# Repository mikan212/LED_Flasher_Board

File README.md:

# LED_Flasher_Board

入力電圧3V
Q1とQ2は裏返してハンダ付けでしてください
| 番号 | 部品 | URL |
|---|---|---|
|R1-R4|390Ω|https://akizukidenshi.com/catalog/g/g125391/|
|R5,R6|10kΩ|https://akizukidenshi.com/catalog/g/g116103/|
|LED|OSW4XME1C1E-100|https://akizukidenshi.com/catalog/g/g106853/|
|C1,C2|100uF|https://akizukidenshi.com/catalog/g/g117877/|
|Q1,Q2|2SD2012|https://akizukidenshi.com/catalog/g/g102510/|
|コネクタ|XH2Pin|https://akizukidenshi.com/catalog/g/g112247/|

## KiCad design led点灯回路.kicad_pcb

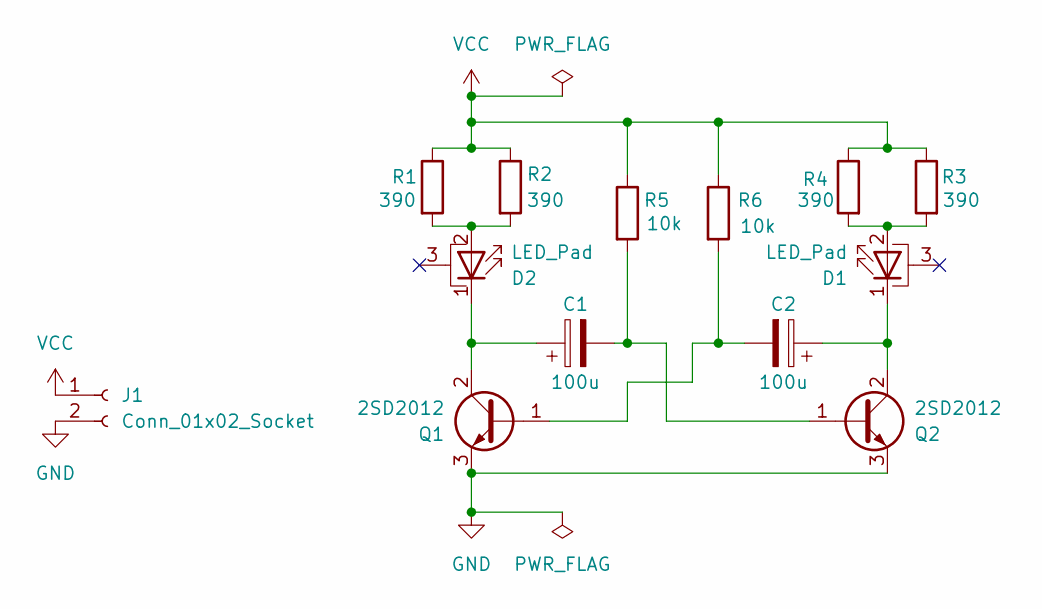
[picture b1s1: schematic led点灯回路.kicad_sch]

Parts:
C1, C2: 100u; CP_Radial_D5.0mm_P2.00mm
D1, D2: LED_Pad; LED_1W_3W_R8
J1: Conn_01x02_Socket; JST_XH_B2B-XH-A_1x02_P2.50mm_Vertical
Q1, Q2: 2SD2012; TO-220F-3_Horizontal_TabUp
R1, R2, R3, R4: 390; R_Axial_DIN0207_L6.3mm_D2.5mm_P10.16mm_Horizontal
R5, R6: 10k; R_Axial_DIN0207_L6.3mm_D2.5mm_P10.16mm_Horizontal

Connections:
GND: J1.2, Q1.3 (E), Q2.3 (E)
unnamed: D1.2 (A), R3.2, R4.2
unnamed: C2.1, D1.1 (K), Q2.2 (C)
unnamed: D2.2 (A), R1.2, R2.2
unnamed: C1.1, D2.1 (K), Q1.2 (C)
unnamed: C2.2, Q1.1 (B), R6.2
unnamed: C1.2, Q2.1 (B), R5.2
VCC: J1.1, R1.1, R2.1, R3.1, R4.1, R5.1, R6.1

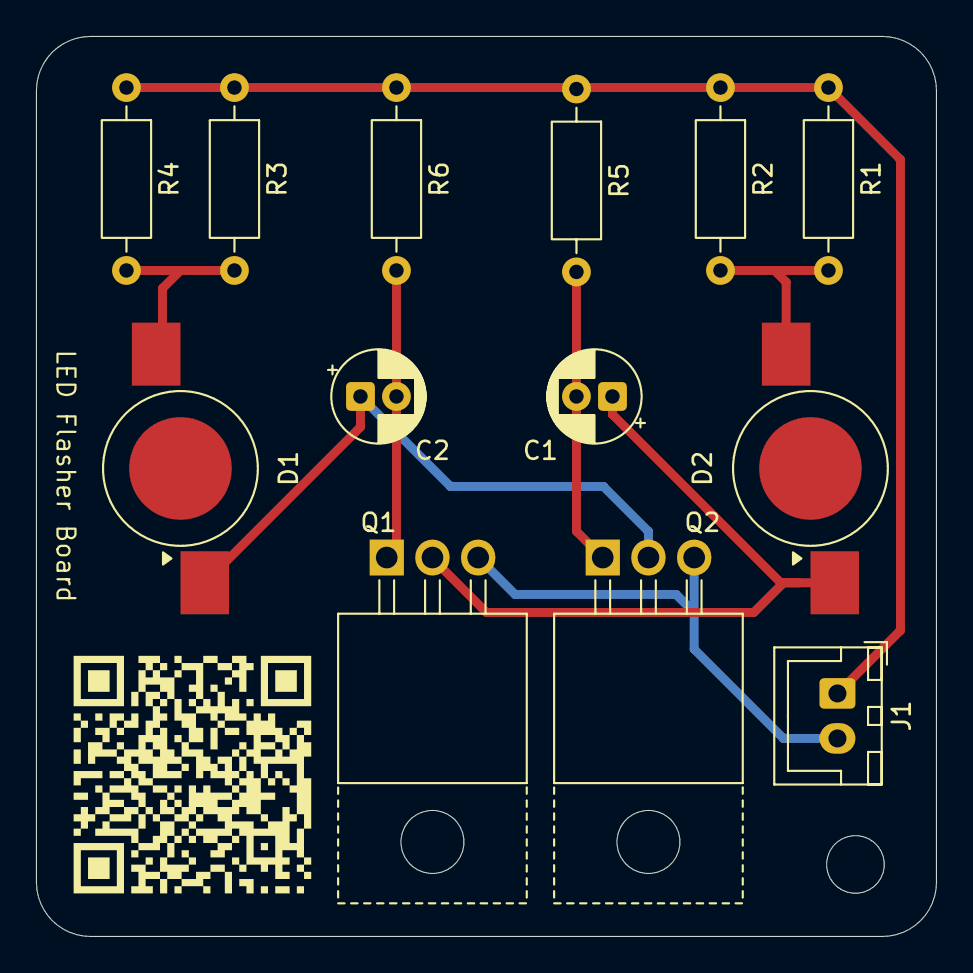
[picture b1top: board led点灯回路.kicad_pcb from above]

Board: 2 copper layers, 50.0 x 50.0 mm, 14 parts (0 on the bottom side), 8 nets.

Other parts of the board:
QR*****: LED_Flasher_Board

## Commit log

2025-06-23 add files
2025-07-15 README.md を更新
